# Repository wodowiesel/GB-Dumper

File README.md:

# GB-Dumper - Gameboy Cartridge Dumper

The GB-Dumper is a **PCB** project for Gameboy cartridge dumps/backups via Arduino __Nano__

&amp; USB-connection with the SPI-Protocol, so you can read ROM and read / write to RAM.

The new configured software and custom PCB is compatible with +5V (mostly USB) Arduino Nano or similar.

Compatibility list:

- Gameboys (Revisions):

:heavy_check_mark: Classic & Original (DMG0 & DMG)

:heavy_check_mark: Color (CGB0 & CGB)

:heavy_check_mark: Pocket & Lite (PGB & LGB)

:heavy_check_mark: Micro (MGB)

:heavy_check_mark: Advance & SP (AGB0 & AGB)

[:heavy_check_mark: BrutzelBoy (BB) custom]

- Cartridges:

:heavy_check_mark: Class/Type A (grey+colors)

:heavy_check_mark: Class B Dual (black)

:heavy_check_mark: Class C (transparent/clear)

:heavy_check_mark: Class D (Advance GBA) -> 3.3V Logic, manual switch

:heavy_check_mark: Class X (special)

:heavy_check_mark: compatibility jumpers for pin 30 /RES + /CS2 
                   & pin 31 VIN/AUDIO + IRQ (functions wip!)

- Functions:

  - GB:

    :heavy_check_mark: Reading full header on PC/Serial

    :heavy_check_mark: Dump ROM on PC

    :heavy_check_mark: Dump RAM on PC

    :heavy_check_mark: Write RAM on Cartridge

    :white_circle: Dump ROM/RAM on SD

  - GBA:

    :heavy_check_mark: Reading full header on PC/Serial

    :white_circle: Dump ROM on PC

    :white_circle: Dump RAM on PC

    :white_circle: Write RAM on Cartridge

    :white_circle: Dump ROM/RAM on SD

# DISCLAIMERS

**This is still "work-in-progress (WIP)/experimental"

I do NOT take any kind of warranty/responsibility for damages/data losses!**

**You can use this at your own risk without guarantees and put device on non conductive surface or enclosure!**

If you like the new design you are free to share it!

Have fun and save the retro world :)

## HARDWARE

- 1x Arduino Nano v3.x (or Uno for old versions) + mini-USB-Cable + IDE

- 1x Custom PCB by WodoWiesel (wodowiesel@quantentunnel.de)

  (or from orig. GBCartReader for Uno)

- 2x flat M3 screws and an enclosure - optional

- 2x SN-74HC595 Shift-Registers from Texas Instruments

- 5x 4,70 kOhm Resistors – pull-ups on active low & impedance matching

- 1x 2-position (3-pin) switch SPDT

- 1x Gameboy Cartridge 32-pin Slot

- 1x push-button - optional

- 1x ~10 uF Capacitor (pol.) - optional/recommended

- 3x Jumpers (required) -> default to GB DMG (marked as dot)

- Female Pin headers/sockets for the chips - or solder it directly

  * 1x 30-pin for Arduino

  * 2x 16-pin for shift register

- Male headers

  * 3x 3-pin (required)

  * 1x 4-pin (I²C RTC/Display - optional)

  * 1x 6-pin (SPI SD-Card - optional)

- 1x Soldering iron

- solder + flux + IPA etc.

## SOFTWARE

- It is based on GBCartRead v1.8 Rev 1.2 - Gameboy Cart Reader by insideGadgets, but impoved and smaller.

- Board based Gameboy Cartridge Reader & Writer which uses

  a C program or Python script to interface via USB with Cartridge directly.

- It allows you to dump your ROM (game), read & write the RAM (saves).

- Works with old Arduino Due-milanove and Uno, but requires wiring & code changes!)

-  Dependencies:

   a. Py

   - Download and install Python 3.2+ or higher (https://www.python.org/download/)

   - Lib: pySerial (https://pypi.python.org/pypi/pyserial/)

   b. C

   - Check dependencies cygwin64 & gcc compiler are installed.

## HOW TO USE

0. Set GB clock-pin jumper to default GND pin (arduino clock only for development/debug purposes 4/16 MHz).

   Reset pin can be set optionally to low to +5V pin if you want to soft-reset control (may need extra code).

1. Open the \GBCartRead_v1.3.x_Arduino_WodoWiesel\GBCartRead_v1.3.x_Arduino_WodoWoiesel.ino file

   with Arduino IDE. Note down and select your COM port number in use (std. Nr.3).

   You can find this out from the Arduino IDE (2) by going to Tools -> Serial port.  

   Then set the identical baudrate as in the py/c-program and flash it to your Arduino.

2. There are two choices to communicate with the Arduino – using the C program or the Python program.

  - Python Program:

  a. Open up the “GB-Dumper-v1.8_Rev1.3.x_Py_Interface.py” script by right clicking it and selecting “Edit with IDLE”.

  b. Then set the identical COM port & baudrate as in the arduino ino-program,

   save and press F5 to run it via py-reader.bat as admin.

  c. A new window will appear, after 2-3 seconds you’ll have some options available.

 - C Program:

   a. Open config.ini and change the COM port & baudrate identical to your Arduino is connected on and save the file.

   b.  Check paths in Makefile and cmaker.bat and run it as admin to compile it.

   c. Run “GBCartRead_v1.3.x_C_Interface.exe” in Windows terminal as admin or re-compile the source for your OS.

3. At this stage you should insert your Gameboy cartridge and press the power button,

   the power LED should light up.

4. Press 0 to read the header and verify that it looks correct. If it doesn’t look correct,

   press the power button to power off the Gameboy cartridge, remove and re-insert it and power it up again.

5. Press 1 to Dump the ROM, 2 to Backup your RAM or 3 to Load your RAM file.

   Hashes (#) will start printing every few seconds and a file called <gametitle>[.gb]

   or *.sav will be created if you chose option 1 or 2.

   If you choose option 3, it will load the save from <gametitle>.sav.

   It’s a good idea to verify your save files too by running the ROM when the save file is present in BGB.

## SPECIALS, CHECKSUMS & MEMORY

1. There are some cartridges which don't quite conform to cartridge header standards or require something out of the ordinary.
   
   For example the EVERDRIVE cartridges uses .srm instead of the more common .sav format and consumes less power than the EZ-Flash.
   
   For further technical infos and datasheets take a good look into the Documentation folder!!

3. GB audio pin (VIN analog) / IRQ (digital) base function is already built-in (wip!), but needs changes for rare games! :construction:

   The /RST and /CS2 pins got own compatibility functions thanks to [joaopauloap](https://github.com/joaopauloap/arduino-gba-dumper).

4. Formatting

   If you're on Linux or Mac make sure the Windows style line endings (CRLF) don't get removed and write a shell script.

5. CRC/Verification/Validation

   This file [GB/C](/docs/gb.txt) stores the ROM names and the CRC32 checksums of the complete ROM and are used only for

   verification at the end of the dumping process.

   Example:

   From: [OSCR](https://github.com/sanni/cartreader/tree/master/sd/)

   Name: 007 - The World Is Not Enough (USA, Europe).gb

   CRC32: E038E666

   It is recommend verifying your Gameboy ROM using BGB (a Gameboy emulator) or

   run validator.bat as admin via ```xgbfix.exe -v -p -d <gametitle>[.gb(c)]``` (should not contain spaces).

   Original can be found in the git project called [ASMotor](https://github.com/asmotor/asmotor/).

   -> My easier validation can be done via the [validator.bat](/code-pc/validator/validator.bat)

   or executable [xgbfix.exe](/code-pc/validator/xgbfix.exe).

6. Memory

  A memory IO-map on the standard GB can be found in the docs [here](/docs/gb-memory-maps.png).

   The file [WisdomTree](/docs/Wisdom_Tree.txt) contains memory address informations and exceptions.

   Additional articles (https://gbdev.gg8.se/wiki/articles/MBC7#Ax8x_-_EEPROM_.28Read.2FWrite.29)

7. CI

   Arduino Workflow [CI](.github/workflows/main.yaml) just for debug.

## REVISION HISTORY

v1.8 Rev 1.3.1 (28 June 2024) by WodoWiesel
- pcb 0.83
- lot more comments and documentation
- CLK switchable (default to GND or unconnected)
- added optional button pin
- added debug test point A0 for mosfet
- /RST & /CS2 (digital) switchable + functions wip
- VIN (analog) & IRQ (digital) switchable + functions wip

v1.8 Rev 1.2 (29 September 2023) by WodoWiesel
- pcb 0.7
- added CRC game informations
- added memory info, links & CI
- adapted pin configuration for new Arduino Nano
- Optimized & detailed Makefile
- added optional display pins
- added logos & pin labels

v1.8 Rev 1.1 (11 March 2022) by WodoWiesel
- pcb v0.6
- added reset pin interrupt
- added pull-up active low resistors
- added Audio/VIN (into the card) pin support for cartridges
- added more stable common ground-plane connectivity
- added M3 mounting holes

-------

v1.8 Rev 1 (28 May 2016)
- Re-add checking for non-printable ASCII characters code that was removed when cleaning up code
- Added custom cartridge files for Wisdom Tree games (thanks Benjamin E.)

v1.8 (21 March 2016)
- Added Nintendo Logo check and compare so you can tell if the cartridge is being read correctly
  (sometimes the title was read ok but the ROM dump wasn't correct)
- Added missing cartridge RAM support
- Cleaned up code

v1.7 Rev 2 (10 February 2016)
- Added checking for non-printable ASCII characters in Gameboy header and replaced them with underscores

v1.7 Rev 1 (17 February 2015)
- Fixed clockPin to change correct port - PB5 (thanks Anna)

v1.7 (7 February 2015) *Only compatible with Gameboy Cart Shield v1.3*
- Added interrupt for button on A1 to switch P-mosfet on A0 that powers the cartridge
- Changed so at startup it doesn't display the Game Cartridge header

v1.6 (3 January 2015)
- Speed increase by using a higher baud rate (400 Kbit from 57.6Kbit) and using hardware SPI (thanks David R.)
- Changed SCK from pin 12 to pin 13 for SPI
- RAM writing speed increase by continually sending 64bytes data from PC and pausing for 5 ms in-between
  (Compatible with Gameboy Cart Shield v1.2 if you connect pins 12 and 13 together)

v1.5 (15 November 2014)
- Speed increases by using direct PORT writing/reading and sending 64 bytes at a time
  (thanks Frode vdM.)
- Compacting functions (thanks Frode vdM.)
- Delays when pulsing WR/RD/MREQ pins reduced to a few NOP cycles

v1.4.2 (14 November 2014)
- Fixed gameTitle array length issue (thanks Frode vdM. and David R.)
- Added Gameboy Camera support (thanks Frode vdM. fvdm1992@yahoo.no)

v1.4.1 (3 January 2014)
- Changed wrPin from pin 13 to A3 to suit Gameboy Cart Shield v1.2

v1.4 (30 August 2013)
- Added gbcartread.exe program for Windows (with source)
  which can be used instead of using the Python script and is a bit faster

v1.3.1 (2 May 2011)
- Updated schematic as R19, R20 and R31 were actually acting as voltage dividers

v1.3 (9 April 2011)
- Added RAM writing ability
- Fixed MBC2 reading RAM overflow relating to the first 4 bits not being ignored properly
- Cleaned up bank select code to use BitRead instead of checking each bit ourselves
- Fixed selecting wrong RAM size when reading
- Fixed incorrect check if RAM was present before reading
- Removed unnecessary changing of data pins to inputs after MBC was initialized when reading RAM

v1.2 (2 April 2011)
- Added RAM saving ability.
- Now prints the amount of data read in 64K increments (i.e. ###64K###128K###192K)
- Changed <gametitle>.rom to <gametitle>.gb

v1.1 (21 March 2011)
- ROM reading is now fully automated.
- The Game Title, MBC type, ROM size and RAM size are presented in the Python script.

v1.0 (19 March 2011)
- Reading ROM only, user to change the maximum ROM bank to read

## CREDITS

 :copyright: 2021-2024 WodoWiesel

 Github (https://github.com/wodowiesel/)

 Twitch (https://www.twitch.com/wodowiesel/)

 Instagram (https://www.instagram.com/wodowiesel)

 YT (https://www.youtube.com/@wodowiesel)

 The new design was checked by the electrical engineer theBrutzler

 (https://github.com/theBrutzler/ & https://www.twitch.com/theBrutzler/)

 => For secondary project for the retro brutzelboy-dumper adapter (https://github.com/wodowiesel/brutzelboy-dumper)

 The new optimized PCB was designed with free KiCAD 8.x software (https://www.kicad.org/)

 :heavy_exclamation_mark: The PCB should be produced at a manufacturer

 (like PCBWay/JLCPCB) with the RoHS lead-free option for environmental protection.

 Original: :copyright: 2011-2016 by [insideGadgets](https://github.com/insidegadgets/GBCartRead/) support@insidegadgets.com

## LICENSES

Not for commercial and/or criminal usage!

- Hardware

   CERN Open Hardware License Version 2 - Weakly Reciprocal

   Short identifier CERN-OHL-W-2.0

   [LICENSE Source](https://spdx.org/licenses/CERN-OHL-W-2.0.html)

- Software

   This work is licensed under a Creative Commons Attribution-NonCommercial 3.0 Unported License.

   [CCANC](http://creativecommons.org/licenses/by-nc/3.0/)

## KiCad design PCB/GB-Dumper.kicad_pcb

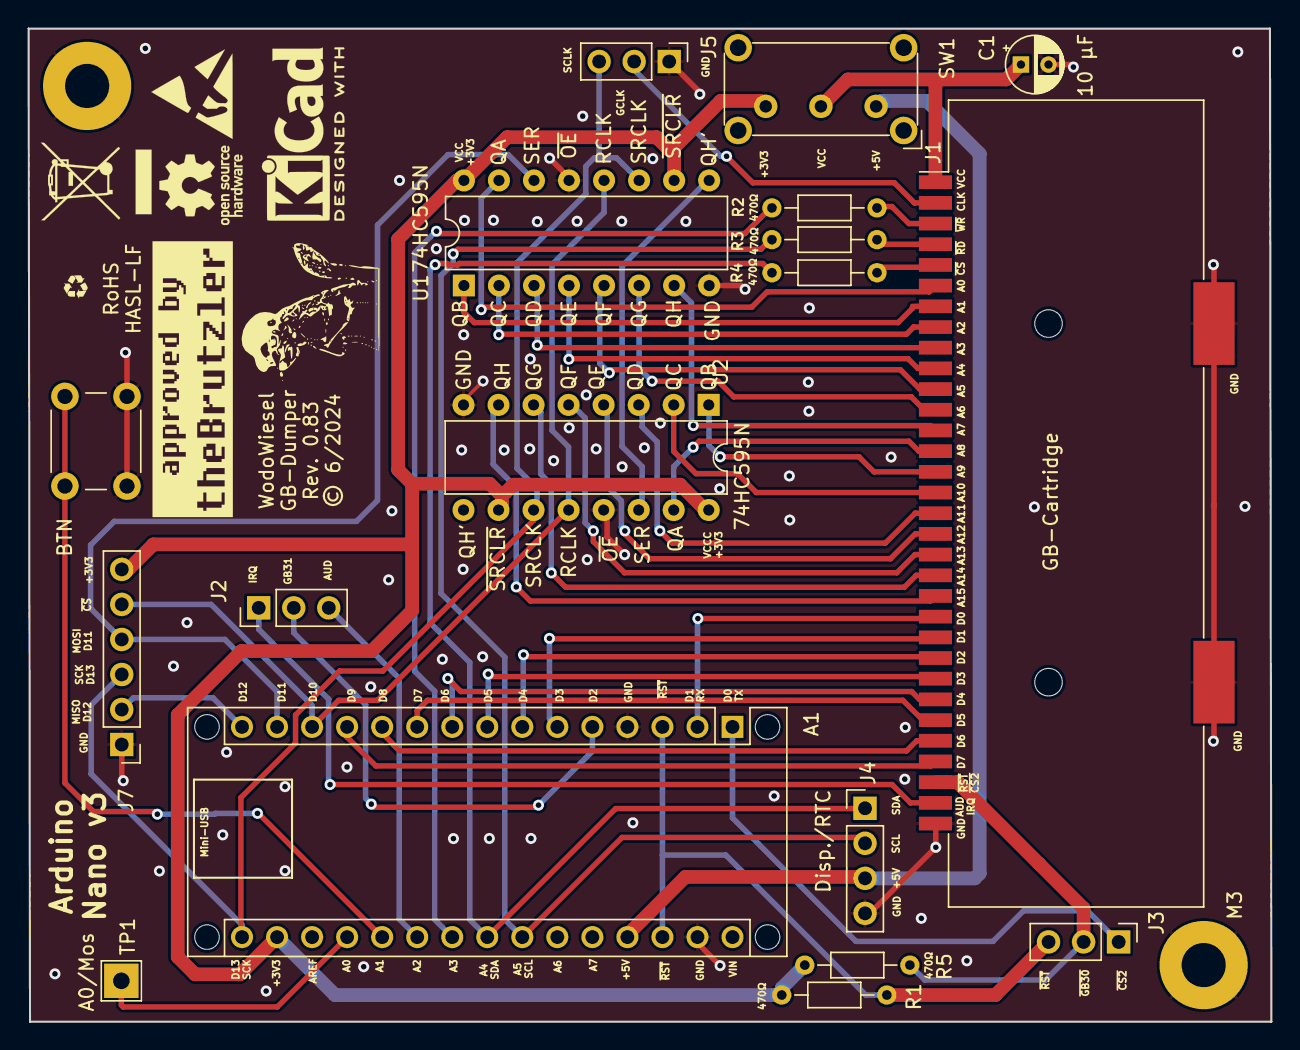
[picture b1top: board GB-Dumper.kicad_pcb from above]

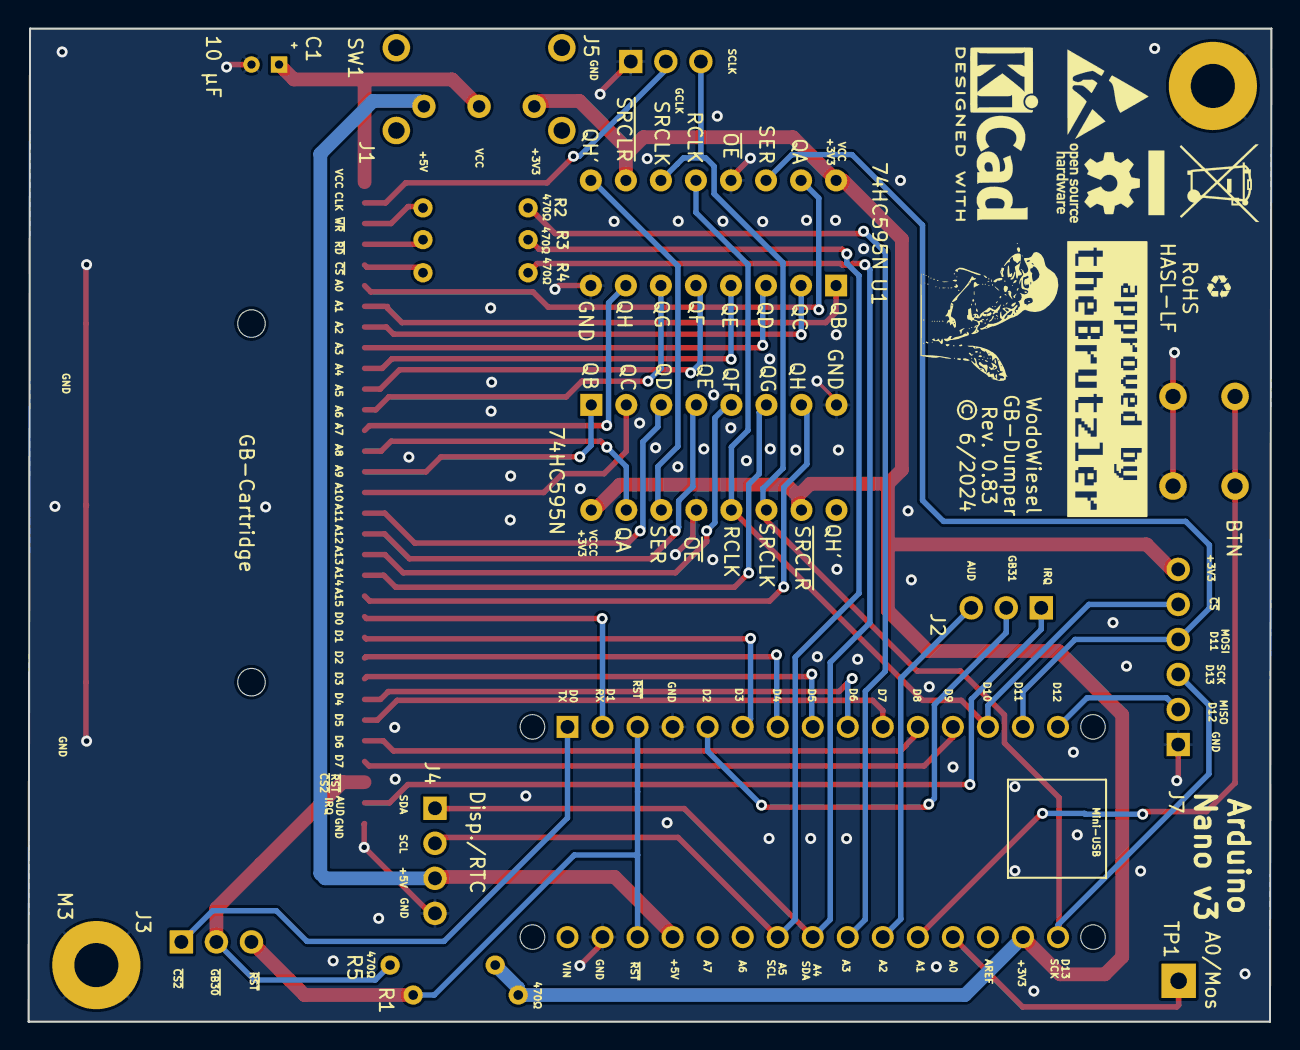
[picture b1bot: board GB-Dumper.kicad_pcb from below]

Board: 2 copper layers, 90.1 x 72.0 mm, 33 parts (7 on the bottom side), 48 nets.

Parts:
A1: Arduino_Nano_v3.x_sorted; Arduino_Nano_WithMountingHoles
BTN: SW_Push; SW_PUSH_6mm
C1: 10 µF; CP_Radial_D4.0mm_P2.00mm
G1, G1*: LOGO; approved_theBrutzler
G2, G2*: LOGO; wiesel-kicad-back-white
G3, G3*: LOGO; recycling-symbol-kicad
J1: GameBoy_Cartridge_MountingPin; GameBoy_Cartridge_AGS_1x32-1MP_P1.50mm_Socket_Horizontal
J2, J3, J5: Conn_01x03_Pin; PinHeader_1x03_P2.54mm_Vertical
J4: Conn_01x04_Pin; PinHeader_1x04_P2.54mm_Vertical
J7: Conn_01x06_Pin; PinHeader_1x06_P2.54mm_Vertical
R1, R2, R3, R4, R5: 470Ω; R_Axial_DIN0204_L3.6mm_D1.6mm_P7.62mm_Horizontal
REF0, REF0*: OSHW-Logo_5.7x6mm_SilkScreen
REF1*, REF2: KiCad-Logo2_5mm_SilkScreen
REF2**: ESD-Logo_6.6x6mm_SilkScreen
REF4*, REF5: WEEE-Logo_5.6x8mm_SilkScreen
REF888**, REF999**: MountingHole_3.2mm_M3_Pad
SW1: SW_SPDT; SW_E-Switch_EG1224_SPDT_Angled
TP1: TestPoint; TestPoint_THTPad_2.5x2.5mm_Drill1.2mm
U1, U2: 74HC595_sorted; DIP-16_W7.62mm

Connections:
GND: A1.4 (GND), A1.29 (GND), BTN.2, C1.2, J1.32 (GND), J1.MP, J4.4, J5.1, J7.1, REF888**.1, REF999**.1, U1.8 (GND), U1.13 (~OE), U2.8 (GND), U2.13 (~OE)
unnamed: A1.17 (+3V3), J7.6, R1.2, R5.2, SW1.3 (C), U1.10 (~SRCLR), U1.16 (VCC), U2.10 (~SRCLR), U2.16 (VCC)
unnamed: A1.27 (+5V), J4.3, SW1.1 (A)
unnamed: A1.19 (A0/PC0), TP1.1
unnamed: A1.20 (A1/PC1), BTN.1
unnamed: A1.21 (A2/PC2), J2.3
unnamed: A1.22 (A3/PC3), R2.1
unnamed: A1.23 (A4/PC4/SDA), J4.1, R4.1
unnamed: A1.24 (A5/PC5/SCL), J4.2, R3.1
unnamed: A1.1 (D0/PD0/TX), J3.1
unnamed: A1.2 (D1/PD1/RX), J1.22 (D0)
unnamed: A1.5 (D2/PD2/INT0), J2.2
unnamed: A1.6 (D3/PD3/INT1), J1.23 (D1)
unnamed: A1.7 (D4/PD4), J1.24 (D2)
unnamed: A1.8 (D5/PD5), J1.25 (D3)
unnamed: A1.9 (D6/PD6), J1.26 (D4)
unnamed: A1.10 (D7/PD7), J1.27 (D5)
unnamed: A1.11 (D8/PB0), J1.28 (D6)
unnamed: A1.12 (D9/PB1), J1.29 (D7)
unnamed: A1.13 (D10/PB2/SS), J7.5, U1.12 (RCLK), U2.12 (RCLK)
unnamed: A1.14 (D11/PB3/MOSI), J7.4, U1.14 (SER)
unnamed: A1.15 (D12/PB4/MISO), J7.2
unnamed: A1.16 (D13/PB5/SCK), J5.3, J7.3, U1.11 (SRCLK), U2.11 (SRCLK)
unnamed: J1.6 (A0), U1.15 (QA)
unnamed: J1.7 (A1), U1.1 (QB)
unnamed: J1.8 (A2), U1.2 (QC)
unnamed: J1.9 (A3), U1.3 (QD)
unnamed: J1.10 (A4), U1.4 (QE)
unnamed: J1.11 (A5), U1.5 (QF)
unnamed: J1.12 (A6), U1.6 (QG)
unnamed: J1.13 (A7), U1.7 (QH)
unnamed: J1.14 (A8), U2.15 (QA)
unnamed: J1.15 (A9), U2.1 (QB)
unnamed: J1.16 (A10), U2.2 (QC)
unnamed: J1.17 (A11), U2.3 (QD)
unnamed: J1.18 (A12), U2.4 (QE)
unnamed: J1.19 (A13), U2.5 (QF)
unnamed: J1.20 (A14), U2.6 (QG)
unnamed: J1.21 (A15), U2.7 (QH)
unnamed: J1.2 (CLK), J5.2
unnamed: C1.1, J1.1 (VCC), SW1.2 (B)
unnamed: J1.31 (VIN), J2.1
unnamed: J1.5 (~CS), R4.2
unnamed: J1.4 (~RD), R3.2
unnamed: J1.30 (~RES), J3.2, R5.1
unnamed: J1.3 (~WR), R2.2
unnamed: A1.3 (~RST/PB6), A1.28 (~RST/PB6), J3.3, R1.1
unnamed: U1.9 (QH'), U2.14 (SER)

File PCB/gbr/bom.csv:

"ID";"Bezeichner";"Footprint";"Stückzahl";"Bezeichnung";"Anbieter und Referenz";
1;"J1";"GameBoy_Cartridge_AGS_1x32-1MP_P1.50mm_Socket_Horizontal";1;"GameBoy_Cartridge_MountingPin";;;
2;"BTN";"SW_PUSH_6mm";1;"SW_Push";;;
3;"U2,U1";"DIP-16_W7.62mm";2;"74HC595_sorted";;;
4;"J4";"PinHeader_1x04_P2.54mm_Vertical";1;"Conn_01x04_Pin";;;
5;"SW1";"SW_E-Switch_EG1224_SPDT_Angled";1;"SW_SPDT";;;
6;"R1,R3,R5,R4,R2";"R_Axial_DIN0204_L3.6mm_D1.6mm_P7.62mm_Horizontal";5;"470Ω";;;
7;"C1";"CP_Radial_D4.0mm_P2.00mm";1;"10 µF";;;
8;"J3,J2,J5";"PinHeader_1x03_P2.54mm_Vertical";3;"Conn_01x03_Pin";;;
9;"TP1";"TestPoint_THTPad_2.5x2.5mm_Drill1.2mm";1;"TestPoint";;;
10;"A1";"Arduino_Nano_WithMountingHoles";1;"Arduino_Nano_v3.x_sorted";;;
11;"J7";"PinHeader_1x06_P2.54mm_Vertical";1;"Conn_01x06_Pin";;;

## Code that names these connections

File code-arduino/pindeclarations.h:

 /*
 UPDATE: This code was changed to be compatible for Arduino NANO and a custom PCB!!

 Author: WodoWiesel
 github: (https://github.com/wodowiesel/GB-Dumper)
 Last Modified: 14 November 2023
 */

#ifndef PINDECLARATIONS_H_
#define PINDECLARATIONS_H_
#define HW6

// AVR definitions for Arduino NANO!
#define PA0 0
#define PA1 1
#define PA2 2
#define PA3 3
#define PA4 4
#define PA5 5
#define PA6 6
#define PA7 7

#define PB0 0
#define PB1 1
#define PB2 2
#define PB3 3
#define PB4 4
#define PB5 5
#define PB6 6
#define PB7 7

#define PC0 0
#define PC1 1
#define PC2 2
#define PC3 3
#define PC4 4
#define PC5 5
#define PC6 6
#define PC7 7

#define PD0 0
#define PD1 1
#define PD2 2
#define PD3 3
#define PD4 4
#define PD5 5
#define PD6 6
#define PD7 7

// Assignment
#define wrPin_high    PORTC |= (1<<PC3); // /WR Pin22 A3
#define wrPin_low     PORTC &= ~(1<<PC3);

#define mreqPin_high  PORTC |= (1<<PC4); // /CS Pin23 A4
#define mreqPin_low   PORTC &= ~(1<<PC4);

#define rdPin_high    PORTC |= (1<<PC5); // /RD Pin24 A5
#define rdPin_low     PORTC &= ~(1<<PC5);

#define latchPin_high PORTB |= (1<<PB2); // RCLK Pin13 D10
#define latchPin_low  PORTB &= ~(1<<PB2);

#define dataPin_high  PORTB |= (1<<PB3); // Pin14 D11
#define dataPin_low   PORTB &= ~(1<<PB3);

#define clockPin_high PORTB |= (1<<PB5); // SRCLK Pin 16 D13
#define clockPin_low  PORTB &= ~(1<<PB5);

#define mosfetPin_high  PORTC  |= (1<<PC0); // Pin19 A0
#define mosfetPin_low   PORTC  &= ~(1<<PC0);

// extra pins
#define gb22Pin_high   PORTD |= (1<<PD2); // GB_D0 Pin5 INT0 D2
#define gb22Pin_low    PORTD &= ~(1<<PD2);

#define gb23Pin_high  PORTD |= (1<<PD3); // GB_D1 Pin6 INT1 D3
#define gb23Pin_low   PORTD &= ~(1<<PD3);

#define gb24Pin_high  PORTD |= (1<<PD4); // GB_D2 Pin7 D4
#define gb24Pin_low   PORTD &= ~(1<<PD4);

#define gb25Pin_high  PORTD |= (1<<PD5); // GB_D3 Pin8 D5
#define gb25Pin_low   PORTD &= ~(1<<PD5);

#define gb26Pin_high  PORTD |= (1<<PD6); // GB_D4 Pin9 D6
#define gb26Pin_low   PORTD &= ~(1<<PD6);

#define gb27Pin_high  PORTD |= (1<<PD7); // GB_D5 Pin10 D7
#define gb27Pin_low   PORTD &= ~(1<<PD7);

#define gb28Pin_high  PORTB |= (1<<PB0); // GB_D6 Pin11 D8
#define gb28Pin_low   PORTB &= ~(1<<PB0);

#define gb29Pin_high  PORTB |= (1<<PB1); // GB_D7 Pin12 D9
#define gb29Pin_low   PORTB &= ~(1<<PB1);

#define gb30Pin_high  PORTB |= ~(1<<PB6); // /RES & CS2 Pin3&29
#define gb30Pin_low   PORTB &= ~(1<<PB6);

#define gb31Pin_high  PORTB |= (1<<PB4); // AUD_IN & IRQ Pin15 D12
#define gb31Pin_low   PORTB &= ~(1<<PB4);

#define gb32Pin_ground 0 //Pin 4&29

#endif /* PINDECLARATIONS_H_ */

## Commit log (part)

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2022-10-03 Initial upload PCB
    Initial upload PCB
2022-10-03 Initial upload PCB 2
    Initial upload PCB 2
2022-10-03 move KiCAD PCB to Folder
    move KiCAD PCB to Folder
2022-10-03 Arduino nano3 pinout & Shift-register manual
    Arduino nano3 pinout & Shift-register manual
2022-10-03 move pictures & manuals into docs
2022-10-03 add Arduino Nano & PC app (py/c) code
2022-10-03 Readme Update
2022-10-03 readme update 2
2022-10-03 readme update 3
2022-10-03 docs cleanup
2022-10-03 LICENSE
    LICENSE
2022-10-04 add urls and fix typos
    add urls and fix typos
2022-10-04 More infos & readability
    More infos & readability
2022-10-04 more credit & note stuff
    more credit & note stuff
2022-10-04 updated changelog & add picture+disclaimer
    updated changelog & add picture+disclaimer
2022-10-04 formatting
2022-10-04 rename wisdom
2022-10-04 cleanup
2022-10-04 cleanup2
2022-10-04 update instructions
    update instructions
2022-10-04 fix typo
    fix typo
2022-10-05 cleanup
    cleanup
2022-10-08 fix typos + ad HW license
    fix typos + ad HW license
2022-10-29 connecor cleanup
2022-10-29 add 3D shapes
2022-10-29 more cleanup
2022-10-29 cleanup readme
2022-12-05 Update README.md
    typos
2023-04-21 docs & ci
2023-04-21 arduino ci
    arduino ci
2023-04-21 hw version
2023-10-13 -update design to 0.7 (clk 6 rst jumpers)
2023-10-13 3d chips
2023-10-13 -optimized resistors, caps, routing -cleanup folders/exports
2023-10-13 fix typo
2023-10-22 -better gnd with mounting holes -cleanup silkscreen -removes orientation crosses -generated new gerbers/exports
2023-10-31 more general documentation and compability-list
2023-11-14 more docs and compatibility, adapted code wip
2023-11-14 rename
2024-02-23 code simplification & more documentation
2024-02-23 better audio + cs2 + rst button support
2024-05-04 cleanup paths & add debug prints
2024-05-04 minor cleanup
2024-05-30 update Readme infos & pinout docu
2024-05-30 better formatting
2024-05-30 more docu
2024-06-01 standardize doc files
2024-06-01 update arduino code to new pcb design + more docu & links
2024-06-28 PCB 0.83 update
2024-06-28 -cs2, res, irq, aud funcs wip -D0 adaption-buton added -many cleanups
2024-06-28 experimental cs2 func impl in loop
2024-06-29 -edge case handling on serial -cs2 docu
2024-08-19 -docu/RM update -batch & make optimizations
2024-08-21 Update README.md
    Update README.md
2024-08-24 update validator batch script
2024-08-24 -added comment on possible flags -added auto padding flag
2024-08-29 update validation infos + cleanup
2024-08-29 add git repo link
2024-10-22 -QOL & print changes -debug & docu info/comments -speed up spi to gb clock 4 mhz -speed up uart baud to 19200
2024-10-22 gb cartridge plug cut
2024-10-22 convert/cast integer on romsize,ramsize,logocheck
2024-10-22 docu for en/decoding
2024-10-24 -minor optimizations
2024-10-29 -more error handling -bump up version
2024-11-19 add done message
2025-01-15 fix path
2025-05-28 Update README.md
    added crosslink
2025-06-04 Update README.md
    fix typos + update compatibility list/status/abrev
2025-10-19 println with F() macro for efficiency
    println with F() macro for efficiency

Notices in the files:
PCB/GB-Dumper.kicad_pcb:
© 6/2024
